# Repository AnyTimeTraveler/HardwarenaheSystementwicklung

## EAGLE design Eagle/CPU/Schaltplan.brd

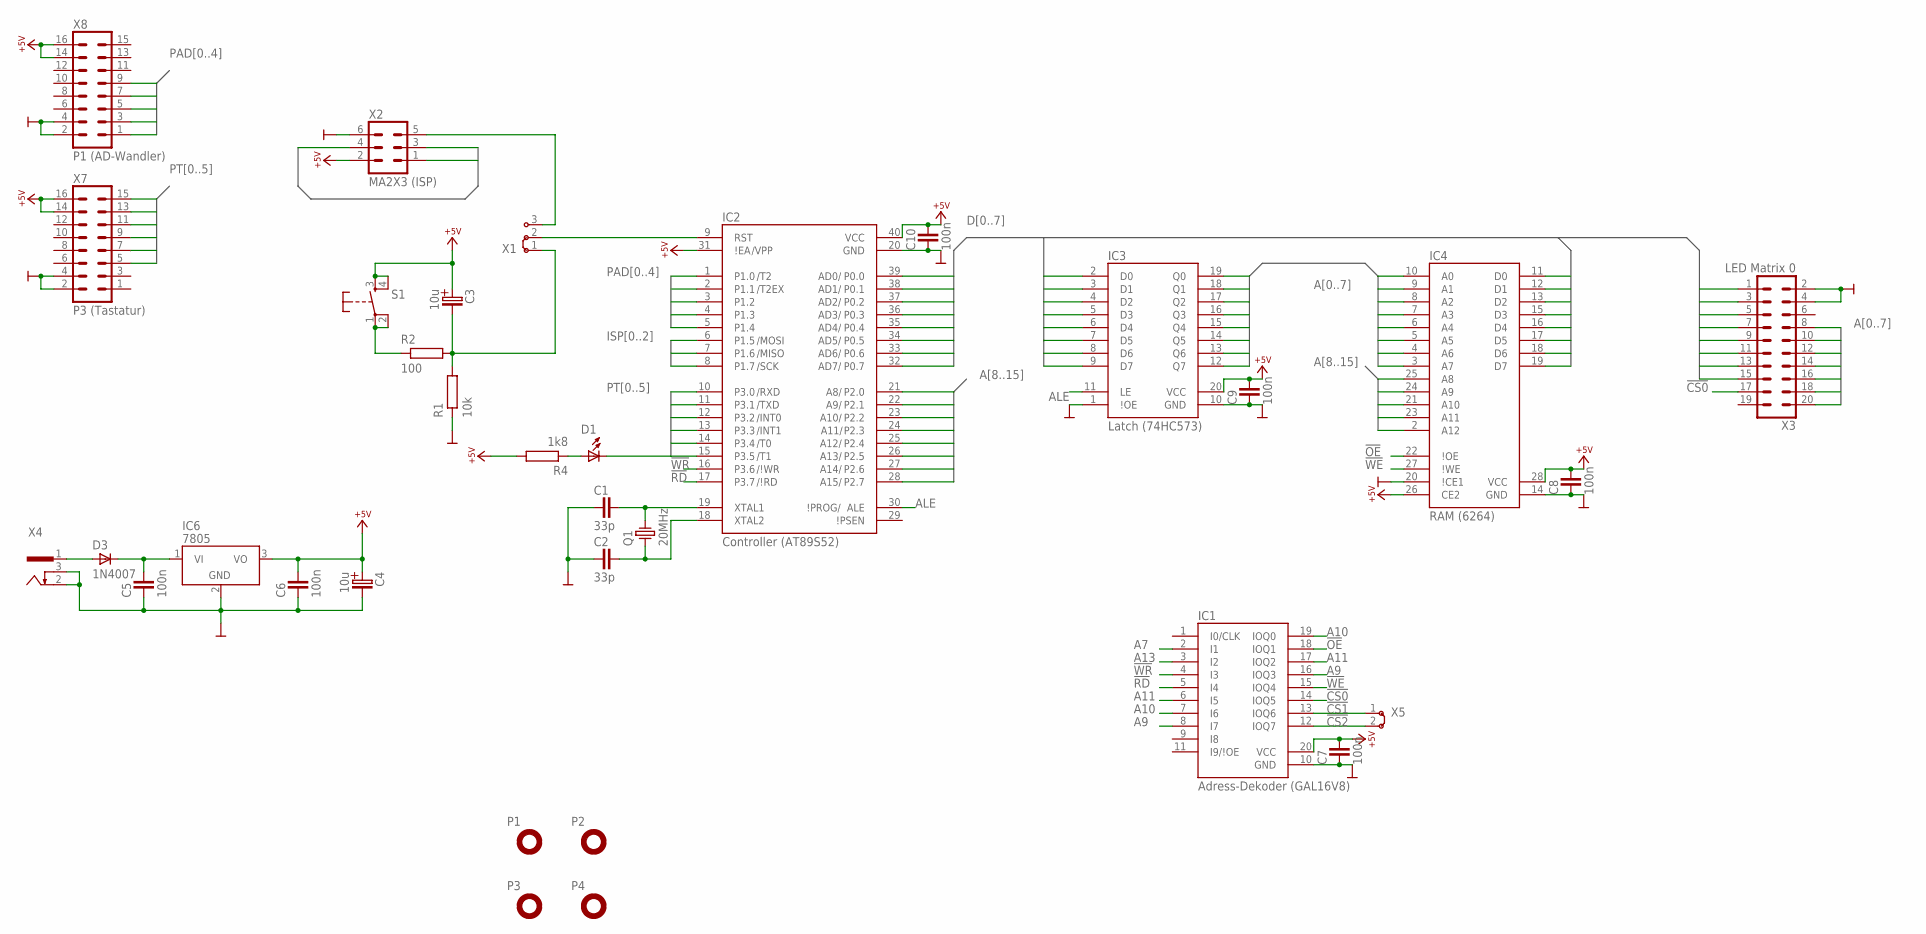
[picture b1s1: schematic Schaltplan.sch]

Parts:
C1, C2: 33p; C-2,5
C3, C4: 10u; ELKO-2,5
C5, C6, C7, C8, C9, C10: 100n; C-2,5
D1: LED3-2,5
D3: 1N4007; DO41-10
IC1: Adress-Dekoder (GAL16V8); DIL20
IC2: Controller (AT89S52); DIL40
IC3: Latch (74HC573); DIL20
IC4: RAM (6264); DIL28
IC6: 7805; TO220V
P1, P2, P3, P4: MPAD-3,0
Q1: 20MHz; HC49U
R1: 10k; R-10
R2: 100; R-10
R4: 1k8; R-10
S1: KEY-3301; T3301
X1: J1X3
X2: MA2X3 (ISP); MA3X2
X3: LED Matrix 0; MA10X2
X4: PWRCON-HEBW21; HEBW21
X5: J1X2
X7: P3 (Tastatur); MA8X2
X8: P1 (AD-Wandler); MA8X2

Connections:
!CS0: IC1.14 (IOQ5), X3.17
!CS1: IC1.13 (IOQ6), X5.1
!CS2: IC1.12 (IOQ7), X5.2
!OE: IC1.18 (IOQ1), IC4.22 (\!OE)
!RD: IC1.5 (I4), IC2.17 (P3.7)
!WE: IC1.15 (IOQ4), IC4.27 (\!WE)
!WR: IC1.4 (I3), IC2.16 (P3.6)
+5V: C3.+, C4.+, C6.2, C7.2, C8.2, C9.2, C10.2, IC1.20 (VCC), IC2.31 (\!EA), IC2.40 (VCC), IC3.20 (VCC), IC4.26 (CE2), IC4.28 (VCC), IC6.3 (VO), R4.2, S1.3 (S), S1.4 (S), X2.2, X7.14, X7.16, X8.14, X8.16
A0: IC3.19 (Q0), IC4.10 (A0), X3.8
A1: IC3.18 (Q1), IC4.9 (A1), X3.10
A2: IC3.17 (Q2), IC4.8 (A2), X3.12
A3: IC3.16 (Q3), IC4.7 (A3), X3.14
A4: IC3.15 (Q4), IC4.6 (A4), X3.16
A5: IC3.14 (Q5), IC4.5 (A5), X3.18
A6: IC3.13 (Q6), IC4.4 (A6), X3.20
A7: IC1.2 (I1), IC3.12 (Q7), IC4.3 (A7)
A8: IC2.21 (P2.0), IC4.25 (A8)
A9: IC1.8 (I7), IC1.16 (IOQ3), IC2.22 (P2.1), IC4.24 (A9)
A10: IC1.7 (I6), IC1.19 (IOQ0), IC2.23 (P2.2), IC4.21 (A10)
A11: IC1.6 (I5), IC1.17 (IOQ2), IC2.24 (P2.3), IC4.23 (A11)
A12: IC2.25 (P2.4), IC4.2 (A12)
A13: IC1.3 (I2), IC2.26 (P2.5)
A14: IC2.27 (P2.6)
A15: IC2.28 (P2.7)
ALE: IC2.30 (ALE), IC3.11 (LE)
D0: IC2.39 (P0.0), IC3.2 (D0), IC4.11 (D0), X3.1
D1: IC2.38 (P0.1), IC3.3 (D1), IC4.12 (D1), X3.3
D2: IC2.37 (P0.2), IC3.4 (D2), IC4.13 (D2), X3.5
D3: IC2.36 (P0.3), IC3.5 (D3), IC4.15 (D3), X3.7
D4: IC2.35 (P0.4), IC3.6 (D4), IC4.16 (D4), X3.9
D5: IC2.34 (P0.5), IC3.7 (D5), IC4.17 (D5), X3.11
D6: IC2.33 (P0.6), IC3.8 (D6), IC4.18 (D6), X3.13
D7: IC2.32 (P0.7), IC3.9 (D7), IC4.19 (D7), X3.15
GND: C1.1, C2.1, C4.-, C5.1, C6.1, C7.1, C8.1, C9.1, C10.1, IC1.10 (GND), IC2.20 (GND), IC3.1 (\!OE), IC3.10 (GND), IC4.14 (GND), IC4.20 (\!CE1), IC6.2 (GND), R1.1, X2.6, X3.2, X3.4, X4.2, X4.3, X7.2, X7.4, X8.2, X8.4
ISP0: IC2.6 (P1.5), X2.4
ISP1: IC2.7 (P1.6), X2.1
ISP2: IC2.8 (P1.7), X2.3
unnamed: D1.A, R4.1
unnamed: IC2.9 (RST), X1.2
unnamed: C1.2, IC2.19 (XTAL1), Q1.2
unnamed: C2.2, IC2.18 (XTAL2), Q1.1
unnamed: D3.A, X4.1
unnamed: C5.2, D3.C, IC6.1 (VI)
unnamed: X1.3, X2.5
unnamed: C3.-, R1.2, R2.2, X1.1
unnamed: R2.1, S1.1, S1.2
PAD0: IC2.1 (P1.0), X8.9
PAD1: IC2.2 (P1.1), X8.7
PAD2: IC2.3 (P1.2), X8.5
PAD3: IC2.4 (P1.3), X8.3
PAD4: IC2.5 (P1.4), X8.1
PT0: IC2.10 (P3.0), X7.15
PT1: IC2.11 (P3.1), X7.13
PT2: IC2.12 (P3.2), X7.11
PT3: IC2.13 (P3.3), X7.9
PT4: IC2.14 (P3.4), X7.7
PT5: D1.C, IC2.15 (P3.5), X7.5

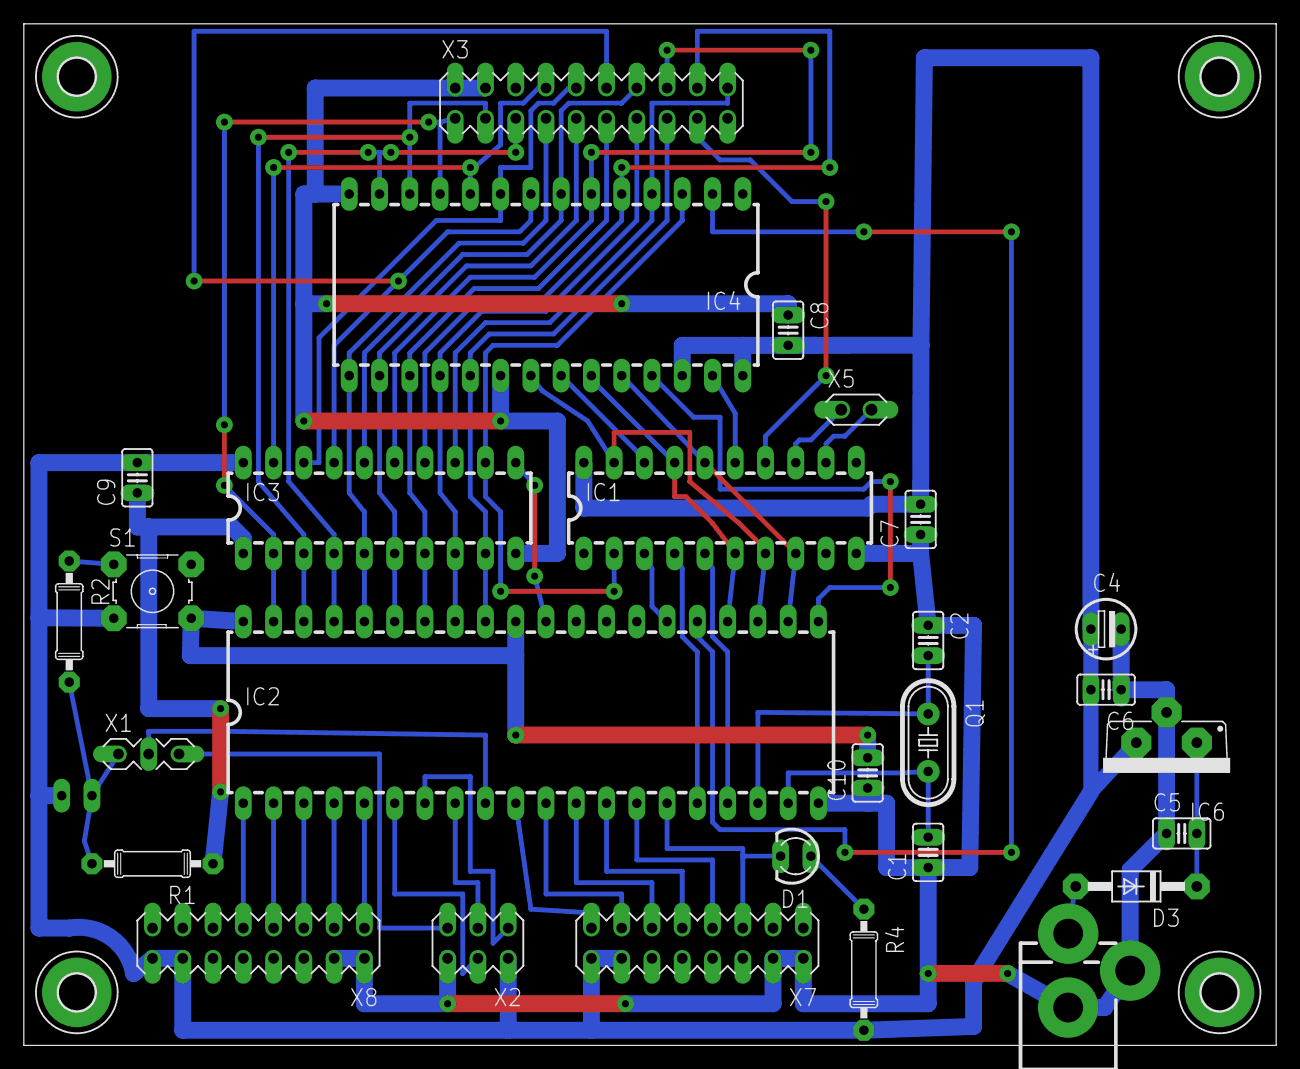
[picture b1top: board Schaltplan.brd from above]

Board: 2 copper layers, 105.1 x 85.7 mm, 33 parts (1 on the bottom side), 55 nets.

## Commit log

2022-11-07 Connect Input devices and clean up a bit, some ERC fixes aswell
2022-11-08 finish schema and start with board
2022-11-16 Further Board allign
2022-11-21 All connected, check schematics
2022-12-28 Screen driver working
2022-12-29 Using register banks for interrupts
2022-12-30 Proper import and export of values and functions
2022-12-31 More work on gameticks and adding pieces
2022-12-31 Fix teris piece encoding
2022-12-31 Fix the damn remove_piece function
2022-12-31 Test: Allocations
2023-01-02 TETRIS PLAYS ITSELF! I'M THE MASTER OF THE UNIVERSE IN 873 BYTES!
2023-01-02 Add full line clearing
2023-01-03 Fix Register Bank 0 Address
2023-01-03 Fix rows falling
2023-01-03 Fix short jump for free keil compiler
2023-01-03 Remove testing code for line clearing
2023-01-11 WIP: Keyboard input
2023-01-13 WIP: Detect baudrate
2023-01-17 Implement baudrate detection
2023-01-17 Add other code to gitignore
2023-01-18 Fix undefined constants
2023-01-18 Add Constant for Debug LED
2023-01-18 Hoefully completed baudrate detection
2023-01-18 Remove unnecessary timer deactivation
2023-01-18 Replace small hack with intended small hack
2023-01-18 Add COLOUR
2023-01-19 Playable in the emulator
2023-01-19 Fix baudrate_detect
2023-01-25 Failed: Add gamestate
2023-01-25 Ignore measurements
2023-01-26 WIP: Reorganizing
2023-01-29 WIP: Refactor
2023-01-29 Fix all the compile errors
2023-02-01 Logic is 2 byte based, screen 3 byte based
2023-02-01 3 Screens work
2023-02-01 WIP: Draw Logo
